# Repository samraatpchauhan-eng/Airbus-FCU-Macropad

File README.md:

# Airbus FCU-Macropad

Airbus-FCU is a scaled replica of the Flight Control Unit found on Airbus aircraft, such as the Airbus A320. It is powered by a **RP Pico 1**, which has the rp2040 chip. It is used to make workflows more efficient, and to convert your desktop into a virtual cockpit! I designed it because as an aviation enthusiast, I wanted to have the ability to integrate aspects of flight and aviation in my day to day life, and I thought that instead of using a generic macropad, why not have it look like the FCU found on the airbus a320!

## Features:
* **Custom Layout:**  6 Cherry MX switches and 4 ec11 switched rotary encoders (10 Keys Total).
* **Quad Encoders:** Quad EC11 Encoders for precise, media adjustments (like brightness, zooming, or volume).
* **Realistic Design:** Engineered with a precise layout matching the real FCU found on the A320, and coordinating most commonly used inputs for an easy to use layout.
* **RP2040 Power:** Driven by the RP2040 chip for rapid response times and effortless flashing.

---

## CAD Model & Case Assembly
Everything fits together precisely using a layered enclosure design. The case includes structural mounting points for the PCB, plates, and components to ensure zero deck-flex during heavy use. Please note the keycaps used in these renders are generic .STEP models downloaded from the internet, and any standard MX keycap should work.

### Case Assembly & Fitment
*A 3D CAD visualization highlighting how the PCB, switches, encoders, and structural enclosure layers interface together seamlessly.*

---

## PCB Design
The underlying electronics were engineered in KiCad. The board features clean routing paths optimized for the RP2040 pin configurations and a direct connection layout to handle both the key switches and rotary encoders.

### Schematic Design
*The circuit schematic mapping the switch routing, and quad encoder connections to the microcontroller.*

### PCB Layout Architecture
*The routed printed circuit board design detailing trace paths, footprints, and physical alignment.*

---

## How to Flash
1. Disconnect the USB cable from the Flight Pad.
2. Press and hold the physical **BOOT** button on the RP2040 controller board.
3. Reconnect the USB cable while holding the button, then release it.
4. A virtual drive named will mount to your operating system.
5. Drag and drop the `airbus_fcu_macropad_default.uf2` binary file directly onto the root of the drive.
6. The device will automatically flash, reboot, and initialize as an operational HID keyboard device.

---

## AI Attribution Note
**Please Note that AI was utilized for some basic project planning and debugging of the Keyboard.JSON, and Keymap.C files in VS.Code**

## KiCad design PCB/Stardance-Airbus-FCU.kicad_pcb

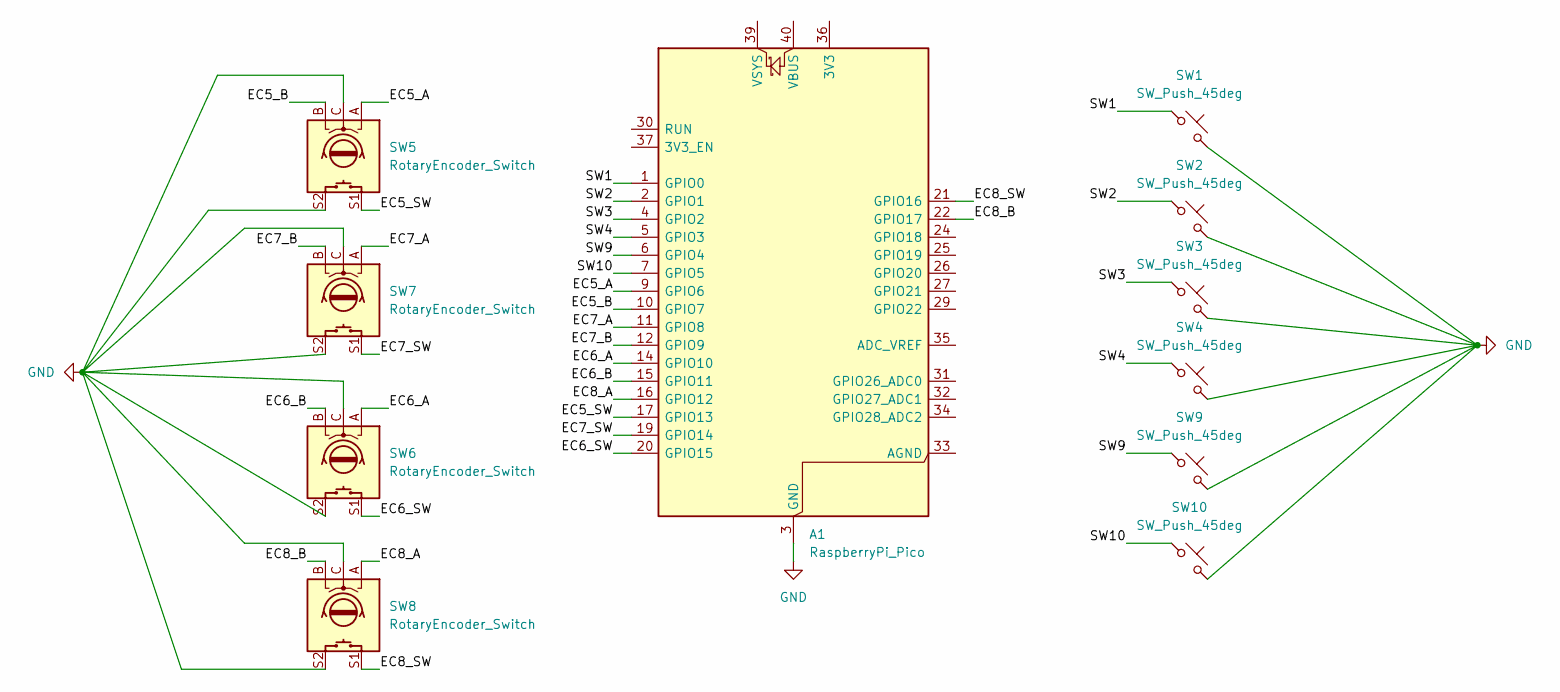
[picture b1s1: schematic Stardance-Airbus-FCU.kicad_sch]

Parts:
A1: RaspberryPi_Pico; RaspberryPi_Pico_Common_THT
SW1, SW2, SW3, SW4, SW9, SW10: SW_Push_45deg; SW_Cherry_MX_1.00u_PCB
SW5, SW6, SW7, SW8: RotaryEncoder_Switch; RotaryEncoder_Alps_EC11E-Switch_Vertical_H20mm_CircularMoun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

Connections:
/EC5_A: A1.9 (GPIO6), SW5.A
/EC5_B: A1.10 (GPIO7), SW5.B
/EC5_SW: A1.17 (GPIO13), SW5.S1
/EC6_A: A1.14 (GPIO10), SW6.A
/EC6_B: A1.15 (GPIO11), SW6.B
/EC6_SW: A1.20 (GPIO15), SW6.S1
/EC7_A: A1.11 (GPIO8), SW7.A
/EC7_B: A1.12 (GPIO9), SW7.B
/EC7_SW: A1.19 (GPIO14), SW7.S1
/EC8_A: A1.16 (GPIO12), SW8.A
/EC8_B: A1.22 (GPIO17), SW8.B
/EC8_SW: A1.21 (GPIO16), SW8.S1
/SW1: A1.1 (GPIO0), SW1.1
/SW2: A1.2 (GPIO1), SW2.1
/SW3: A1.4 (GPIO2), SW3.1
/SW4: A1.5 (GPIO3), SW4.1
/SW9: A1.6 (GPIO4), SW9.1
/SW10: A1.7 (GPIO5), SW10.1
GND: A1.3 (GND), A1.8 (GND), A1.13 (GND), A1.18 (GND), A1.23 (GND), A1.28 (GND), A1.38 (GND), SW1.2, SW2.2, SW3.2, SW4.2, SW5.C, SW5.S2, SW6.C, SW6.S2, SW7.C, SW7.S2, SW8.C, SW8.S2, SW9.2, SW10.2

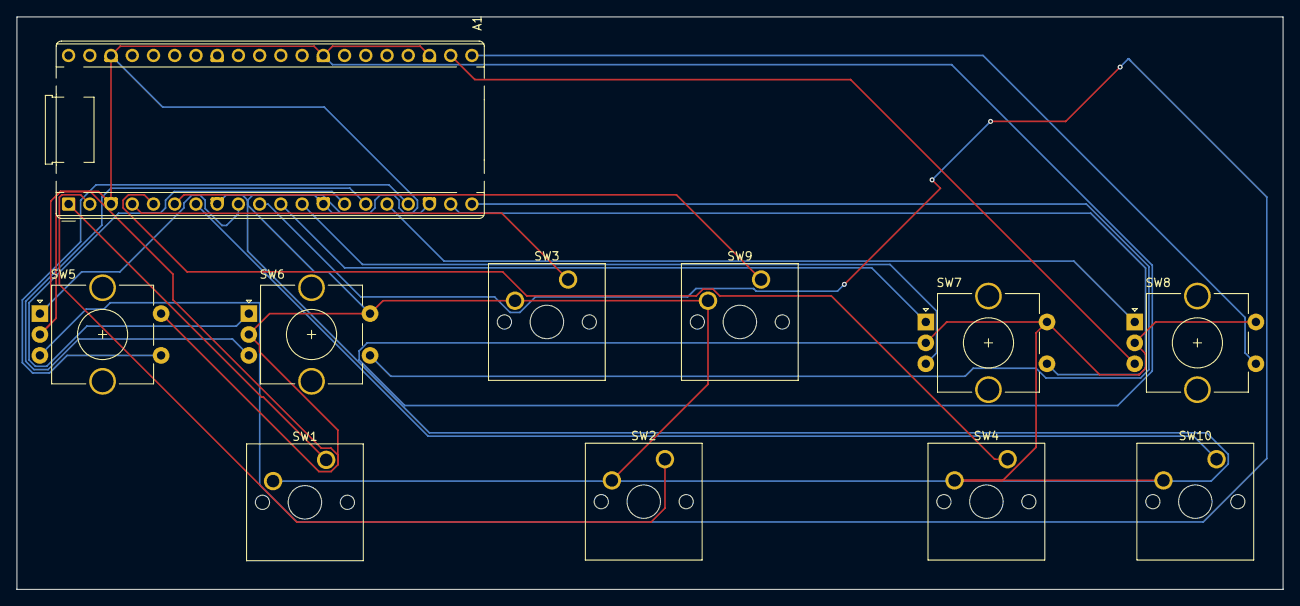
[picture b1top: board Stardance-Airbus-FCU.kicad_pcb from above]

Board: 2 copper layers, 151.5 x 68.5 mm, 11 parts (0 on the bottom side), 19 nets.
